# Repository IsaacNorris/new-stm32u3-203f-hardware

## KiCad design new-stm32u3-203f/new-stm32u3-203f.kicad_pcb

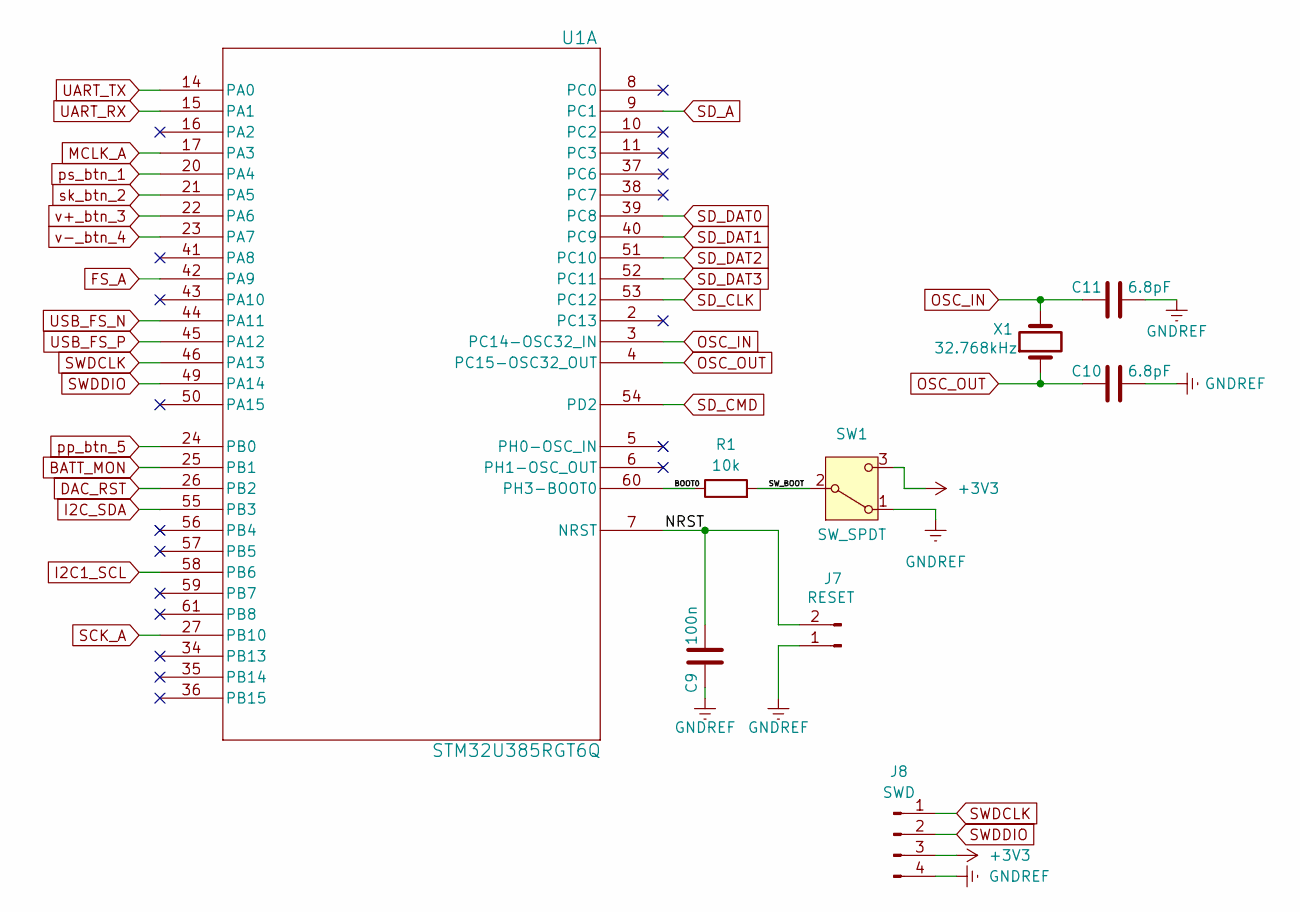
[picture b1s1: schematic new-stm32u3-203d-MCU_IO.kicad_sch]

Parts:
C9: 100n; C_0603_1608Metric
C10, C11: 6.8pF; C_0603_1608Metric
J7: RESET; PinHeader_1x02_P1.00mm_Vertical
J8: SWD; PinHeader_1x04_P2.54mm_Vertical
R1: 10k; R_0603_1608Metric
SW1: SW_SPDT; SW_CJS-1200TA
U1: STM32U385RGT6Q; LQFP-64_10x10mm_P0.5mm
X1: 32.768kHz; Crystal_SMD_3215-2Pin_3.2x1.5mm

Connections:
/MCU_IO/BOOT0: R1.1, U1.60 (PH3-BOOT0)
/MCU_IO/NRST: C9.2, J7.2, U1.7 (NRST)
/MCU_IO/SW_BOOT: R1.2, SW1.2 (B)
AVDD: J8.3, SW1.3 (C); also elsewhere on the board
BATT_MON: U1.25 (PB1); also elsewhere on the board
DAC_RST: U1.26 (PB2); also elsewhere on the board
FS_A: U1.42 (PA9); also elsewhere on the board
I2C1_SCL: U1.58 (PB6); also elsewhere on the board
I2C_SDA: U1.55 (PB3); also elsewhere on the board
MCLK_A: U1.17 (PA3); also elsewhere on the board
OSC_IN: C11.1, U1.3 (PC14-OSC32_IN), X1.2
OSC_OUT: C10.1, U1.4 (PC15-OSC32_OUT), X1.1
SCK_A: U1.27 (PB10); also elsewhere on the board
SD_A: U1.9 (PC1); also elsewhere on the board
SD_CLK: U1.53 (PC12); also elsewhere on the board
SD_CMD: U1.54 (PD2); also elsewhere on the board
SD_DAT0: U1.39 (PC8); also elsewhere on the board
SD_DAT1: U1.40 (PC9); also elsewhere on the board
SD_DAT2: U1.51 (PC10); also elsewhere on the board
SD_DAT3: U1.52 (PC11); also elsewhere on the board
SWDCLK: J8.1, U1.46 (PA13)
SWDDIO: J8.2, U1.49 (PA14)
UART_RX: U1.15 (PA1); also elsewhere on the board
UART_TX: U1.14 (PA0); also elsewhere on the board
UBS_D+: U1.45 (PA12); also elsewhere on the board
USB_D-: U1.44 (PA11); also elsewhere on the board
USB_GND: C9.1, C10.2, C11.2, J7.1, J8.4, SW1.1 (A); also elsewhere on the board
pp_btn_5: U1.24 (PB0); also elsewhere on the board
ps_btn_1: U1.20 (PA4); also elsewhere on the board
sk_btn_2: U1.21 (PA5); also elsewhere on the board
v+_btn_3: U1.22 (PA6); also elsewhere on the board
v-_btn_4: U1.23 (PA7); also elsewhere on the board

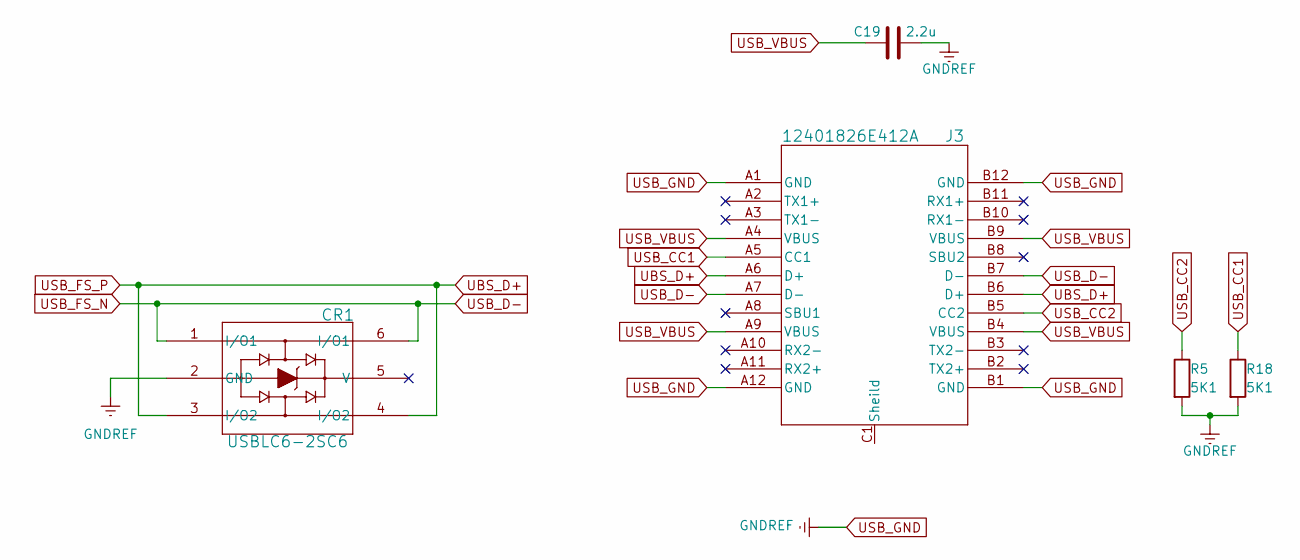
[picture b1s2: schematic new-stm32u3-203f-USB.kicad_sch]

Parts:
C19: 2.2u; C_0603_1608Metric
CR1: USBLC6-2SC6; SOT23-6L_STM
J3: 12401826E412A; 12401826_AMP
R5, R18: 5K1; R_0603_1608Metric

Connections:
UBS_D+: CR1.3 (I/O2), CR1.4 (I/O2), J3.A6 (D+), J3.B6 (D+); also elsewhere on the board
USB_3v3_EN: C19.1, J3.A4 (VBUS), J3.A9 (VBUS), J3.B4 (VBUS), J3.B9 (VBUS); also elsewhere on the board
USB_CC1: J3.A5 (CC1), R18.1
USB_CC2: J3.B5 (CC2), R5.1
USB_D-: CR1.1 (I/O1), CR1.6 (I/O1), J3.A7 (D-), J3.B7 (D-); also elsewhere on the board
USB_GND: C19.2, CR1.2 (GND), J3.A1 (GND), J3.A12 (GND), J3.B1 (GND), J3.B12 (GND), R5.2, R18.2; also elsewhere on the board

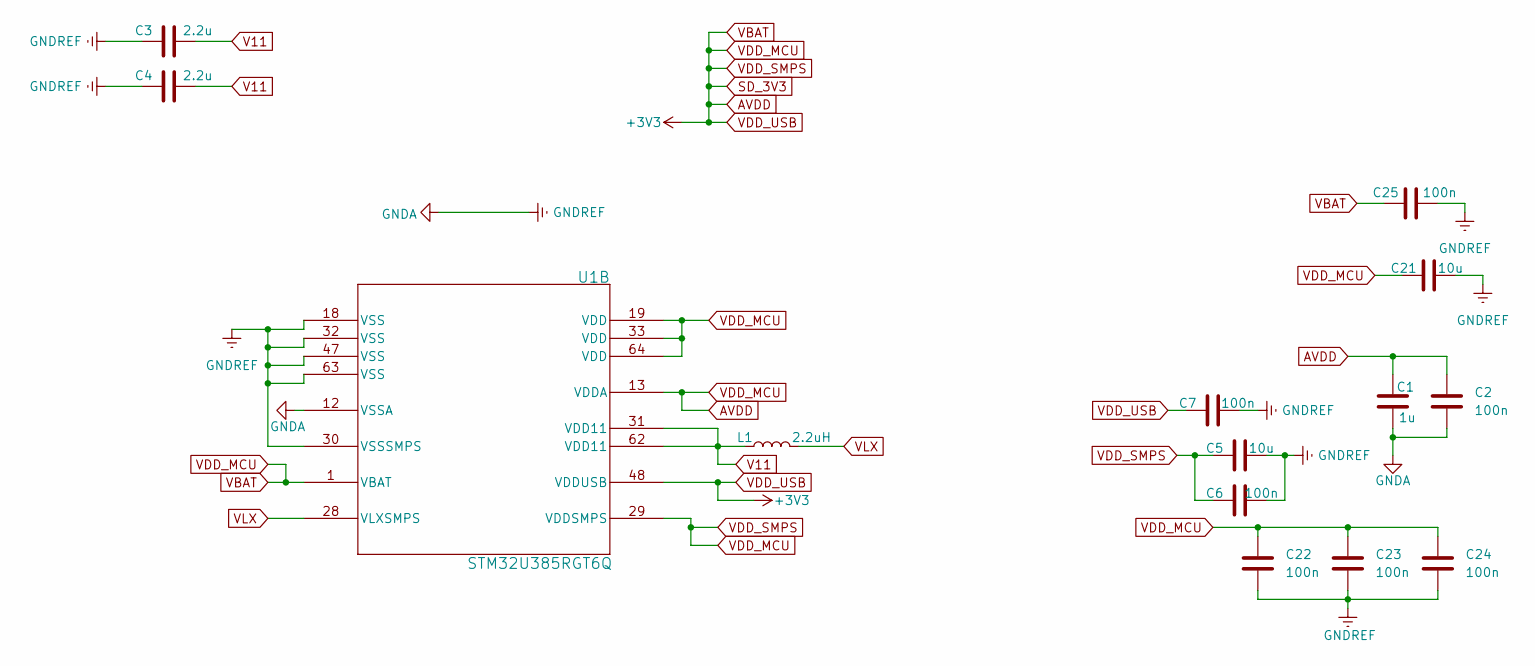
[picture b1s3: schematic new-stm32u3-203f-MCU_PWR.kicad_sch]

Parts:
C1: 1u; C_0603_1608Metric
C2, C6, C7, C22, C23, C24, C25: 100n; C_0603_1608Metric
C3, C4: 2.2u; C_0603_1608Metric
C5, C21: 10u; C_0603_1608Metric
L1: 2.2uH; L_0603_1608Metric
U1: STM32U385RGT6Q; LQFP-64_10x10mm_P0.5mm

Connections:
AVDD: C1.2, C2.2, C5.2, C6.2, C7.2, C21.2, C22.2, C23.2, C24.2, C25.2, U1.1 (VBAT), U1.13 (VDDA), U1.19 (VDD), U1.29 (VDDSMPS), U1.33 (VDD), U1.48 (VDDUSB), U1.64 (VDD); also elsewhere on the board
USB_GND: C1.1, C2.1, C3.2, C4.2, C5.1, C6.1, C7.1, C21.1, C22.1, C23.1, C24.1, C25.1, U1.12 (VSSA), U1.18 (VSS), U1.30 (VSSSMPS), U1.32 (VSS), U1.47 (VSS), U1.63 (VSS); also elsewhere on the board
V11: C3.1, C4.1, L1.1, U1.31 (VDD11), U1.62 (VDD11)
VLX: L1.2, U1.28 (VLXSMPS)

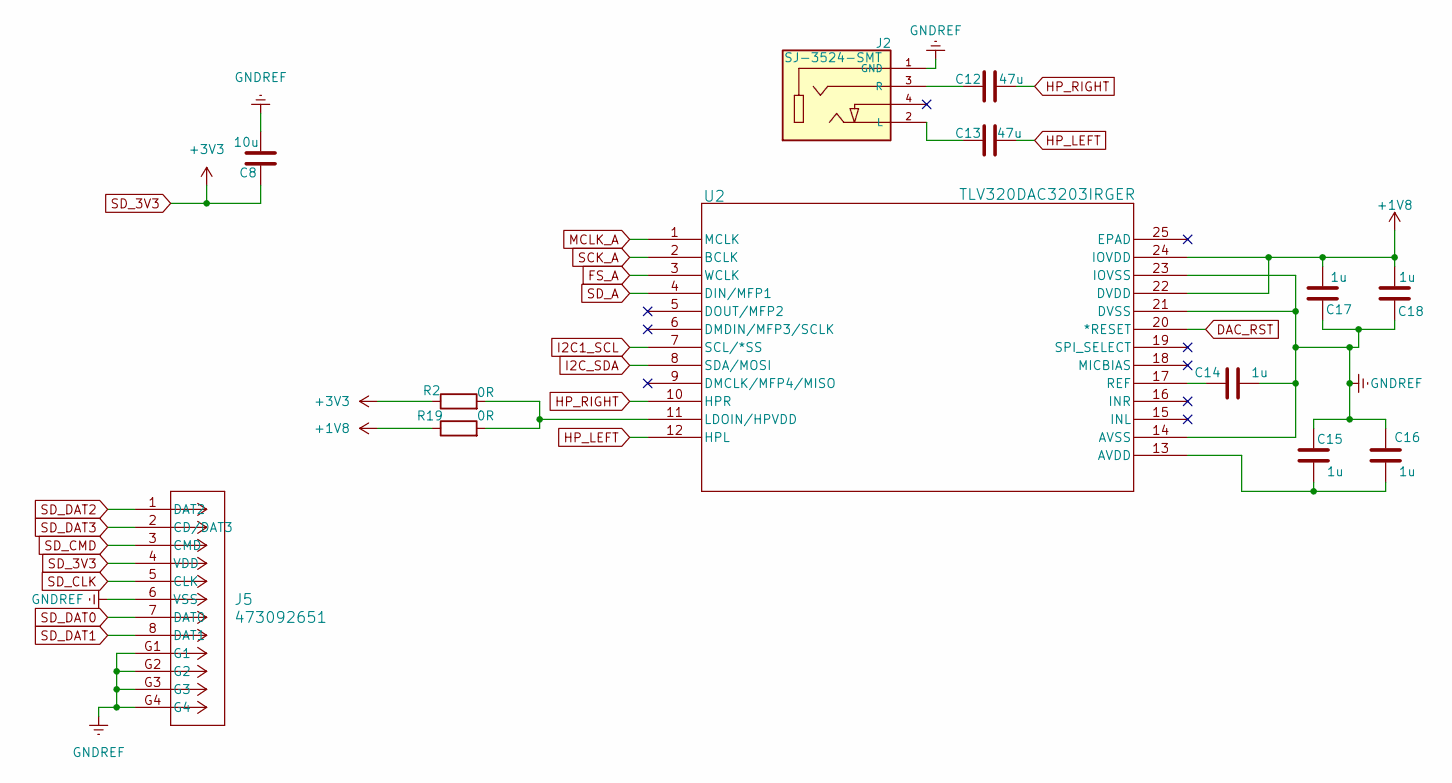
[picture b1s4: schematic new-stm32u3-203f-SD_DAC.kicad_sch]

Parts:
C8: 10u; C_0603_1608Metric
C12, C13: 47u; C_0603_1608Metric
C14, C15, C16, C17, C18: 1u; C_0603_1608Metric
J2: SJ-3524-SMT; Jack_3.5mm_CUI_SJ-3524-SMT_Horizontal; PARTREV 1.03
J5: 473092651; CONN12_47309-2651_MOL
R2, R19: 0R; R_0603_1608Metric
U2: TLV320DAC3203IRGER; Texas_RGE0024C_VQFN-24-1EP_4x4mm_P0.5mm_EP2.1x2.1mm

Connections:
+1V8: C17.2, C18.2, R19.1, U2.22 (DVDD), U2.24 (IOVDD); also elsewhere on the board
AVDD: C8.2, J5.4 (VDD), R2.1; also elsewhere on the board
DAC_RST: U2.20 (*RESET); also elsewhere on the board
FS_A: U2.3 (WCLK); also elsewhere on the board
HP_LEFT: C13.2, U2.12 (HPL)
HP_RIGHT: C12.2, U2.10 (HPR)
I2C1_SCL: U2.7 (SCL/*SS); also elsewhere on the board
I2C_SDA: U2.8 (SDA/MOSI); also elsewhere on the board
MCLK_A: U2.1 (MCLK); also elsewhere on the board
unnamed: C13.1, J2.2 (L), J2.T
unnamed: C12.1, J2.3 (R), J2.R
unnamed: C15.2, C16.2, U2.13 (AVDD)
unnamed: R2.2, R19.2, U2.11 (LDOIN/HPVDD)
unnamed: C14.1, U2.17 (REF)
SCK_A: U2.2 (BCLK); also elsewhere on the board
SD_A: U2.4 (DIN/MFP1); also elsewhere on the board
SD_CLK: J5.5 (CLK); also elsewhere on the board
SD_CMD: J5.3 (CMD); also elsewhere on the board
SD_DAT0: J5.7 (DAT0); also elsewhere on the board
SD_DAT1: J5.8 (DAT1); also elsewhere on the board
SD_DAT2: J5.1 (DAT2); also elsewhere on the board
SD_DAT3: J5.2 (CD/DAT3); also elsewhere on the board
USB_GND: C8.1, C14.2, C15.1, C16.1, C17.1, C18.1, J2.1 (GND), J2.S, J5.6 (VSS), J5.G1, J5.G2, J5.G3, J5.G4, U2.14 (AVSS), U2.21 (DVSS), U2.23 (IOVSS); also elsewhere on the board

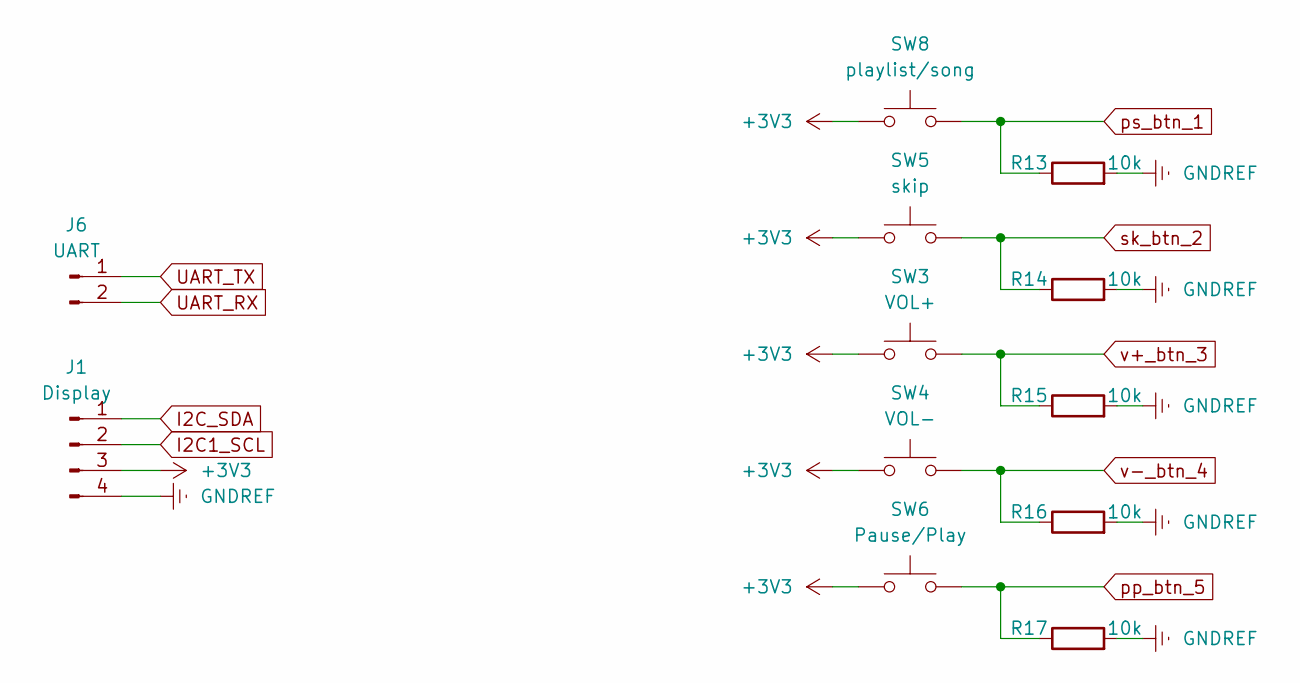
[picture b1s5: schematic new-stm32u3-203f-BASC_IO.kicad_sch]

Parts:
J1: Display; PinHeader_1x04_P2.54mm_Vertical
J6: UART; PinHeader_1x02_P2.54mm_Vertical
R13, R14, R15, R16, R17: 10k; R_0603_1608Metric
SW3: VOL+; Panasonic_EVQPUL_EVQPUC
SW4: VOL-; Panasonic_EVQPUL_EVQPUC
SW5: skip; Panasonic_EVQPUL_EVQPUC
SW6: Pause/Play; Panasonic_EVQPUL_EVQPUC
SW8: playlist/song; Panasonic_EVQPUL_EVQPUC

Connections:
AVDD: J1.3, SW3.1, SW4.1, SW5.1, SW6.1, SW8.1; also elsewhere on the board
I2C1_SCL: J1.2; also elsewhere on the board
I2C_SDA: J1.1; also elsewhere on the board
UART_RX: J6.2; also elsewhere on the board
UART_TX: J6.1; also elsewhere on the board
USB_GND: J1.4, R13.2, R14.2, R15.2, R16.2, R17.2; also elsewhere on the board
pp_btn_5: R17.1, SW6.2; also elsewhere on the board
ps_btn_1: R13.1, SW8.2; also elsewhere on the board
sk_btn_2: R14.1, SW5.2; also elsewhere on the board
v+_btn_3: R15.1, SW3.2; also elsewhere on the board
v-_btn_4: R16.1, SW4.2; also elsewhere on the board

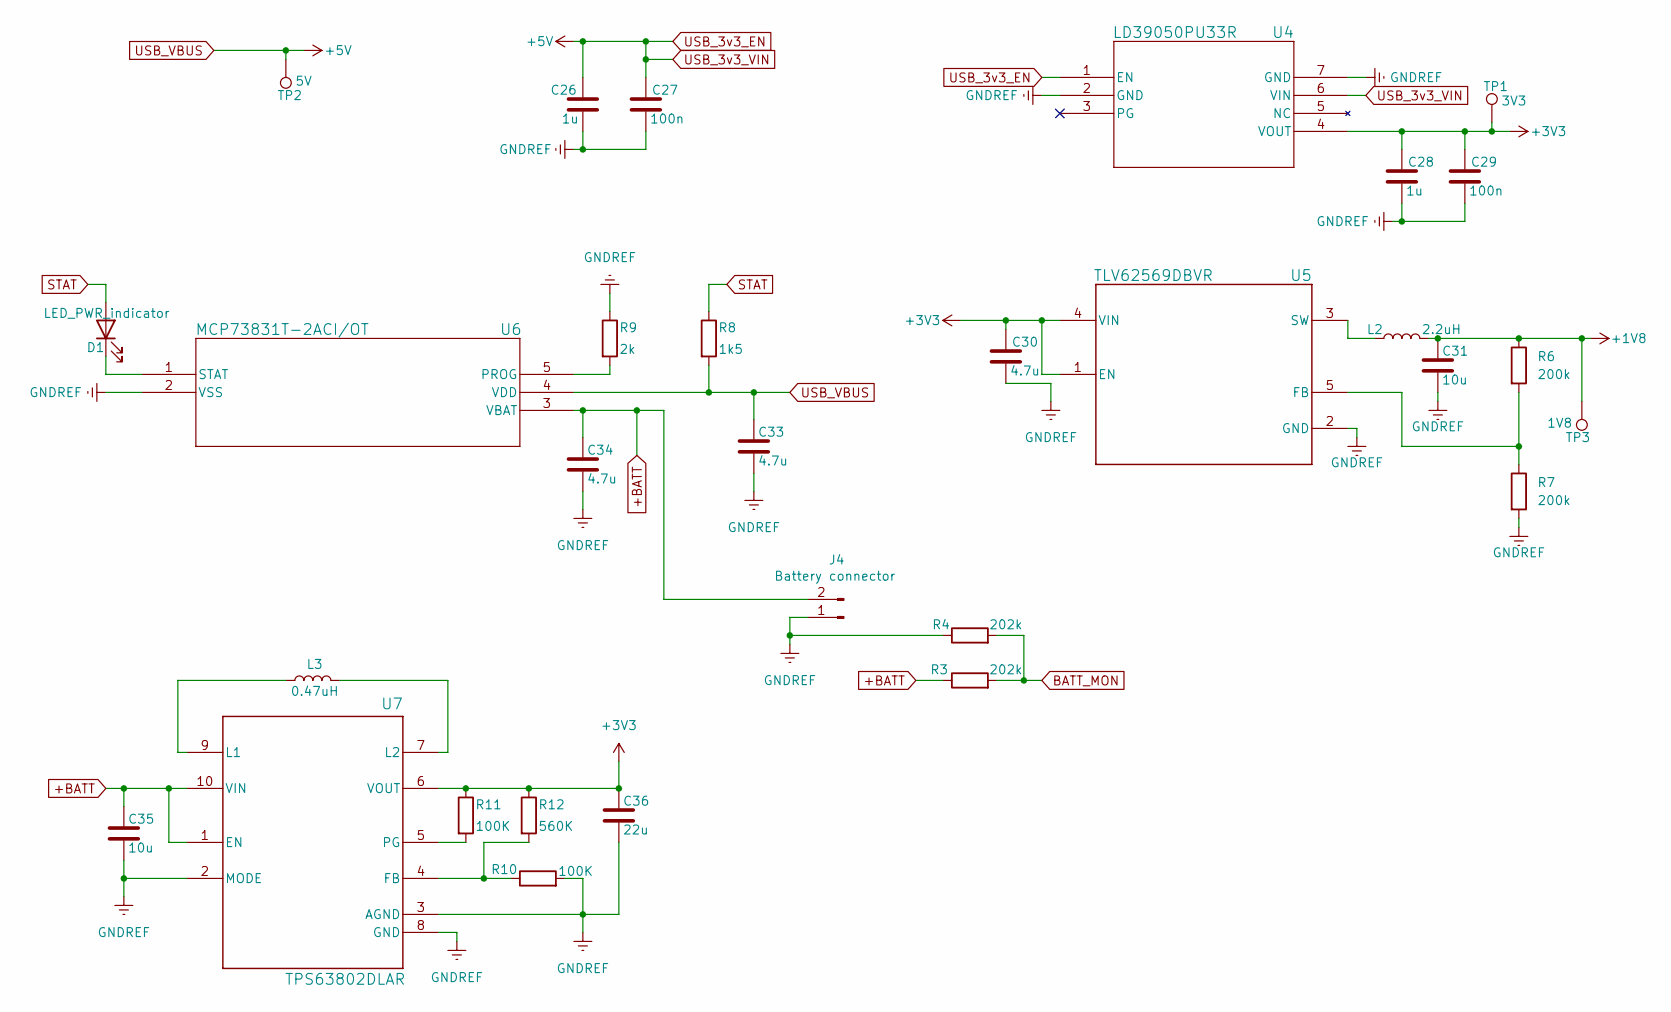
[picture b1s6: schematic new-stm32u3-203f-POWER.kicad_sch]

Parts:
C26, C28: 1u; C_0603_1608Metric
C27, C29: 100n; C_0603_1608Metric
C30, C33, C34: 4.7u; C_0603_1608Metric
C31, C35: 10u; C_0603_1608Metric
C36: 22u; C_0603_1608Metric
D1: LED_PWR_indicator; LED_0603_1608Metric
J4: Battery connector; PinHeader_1x02_P2.54mm_Vertical
L2: 2.2uH; L_0603_1608Metric
L3: 0.47uH; L_0603_1608Metric
R3, R4: 202k; R_0603_1608Metric
R6, R7: 200k; R_0603_1608Metric
R8: 1k5; R_0603_1608Metric
R9: 2k; R_0603_1608Metric
R10, R11: 100K; R_0603_1608Metric
R12: 560K; R_0603_1608Metric
TP1: 3V3; TestPoint_Pad_D1.0mm
TP2: 5V; TestPoint_Pad_D1.0mm
TP3: 1V8; TestPoint_Pad_D1.0mm
U4: LD39050PU33R; DFN-6-1EP_3x3mm_P0.95mm_EP1.7x2.6mm
U5: TLV62569DBVR; SOT-23-5
U6: MCP73831T-2ACI/OT; SOT-23-5
U7: TPS63802DLAR; DLA0010A

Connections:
+1V8: C31.2, L2.2, R6.1, TP3.1; also elsewhere on the board
+BATT: C34.2, C35.2, J4.2, R3.1, U6.3 (VBAT), U7.1 (EN), U7.10 (VIN)
AVDD: C28.2, C29.2, C30.2, C36.2, R11.1, R12.1, TP1.1, U4.4 (VOUT), U5.1 (EN), U5.4 (VIN), U7.6 (VOUT); also elsewhere on the board
BATT_MON: R3.2, R4.2; also elsewhere on the board
unnamed: D1.1 (K), U6.1 (STAT)
unnamed: R6.2, R7.1, U5.5 (FB)
unnamed: L2.1, U5.3 (SW)
unnamed: R9.2, U6.5 (PROG)
unnamed: R10.1, R12.2, U7.4 (FB)
unnamed: L3.1, U7.9 (L1)
unnamed: L3.2, U7.7 (L2)
unnamed: R11.2, U7.5 (PG)
STAT: D1.2 (A), R8.1
USB_3v3_EN: C26.2, C27.2, C33.2, R8.2, TP2.1, U4.1 (EN), U4.6 (VIN), U6.4 (VDD); also elsewhere on the board
USB_GND: C26.1, C27.1, C28.1, C29.1, C30.1, C31.1, C33.1, C34.1, C35.1, C36.1, J4.1, R4.1, R7.2, R9.1, R10.2, U4.2 (GND), U4.7 (GND), U5.2 (GND), U6.2 (VSS), U7.2 (MODE), U7.3 (AGND), U7.8 (GND); also elsewhere on the board

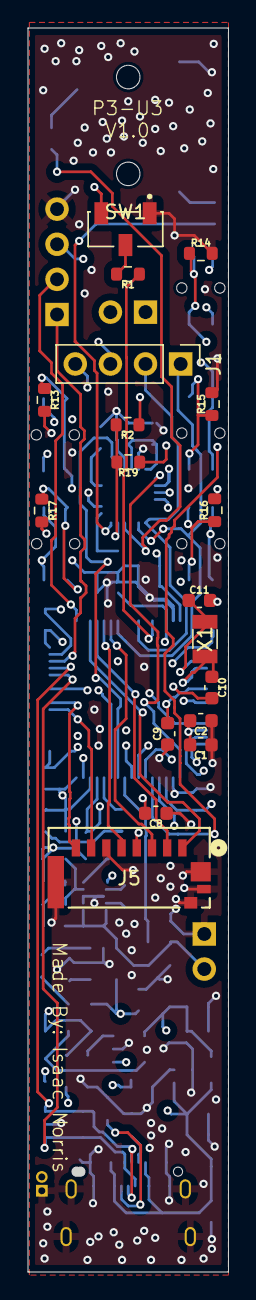
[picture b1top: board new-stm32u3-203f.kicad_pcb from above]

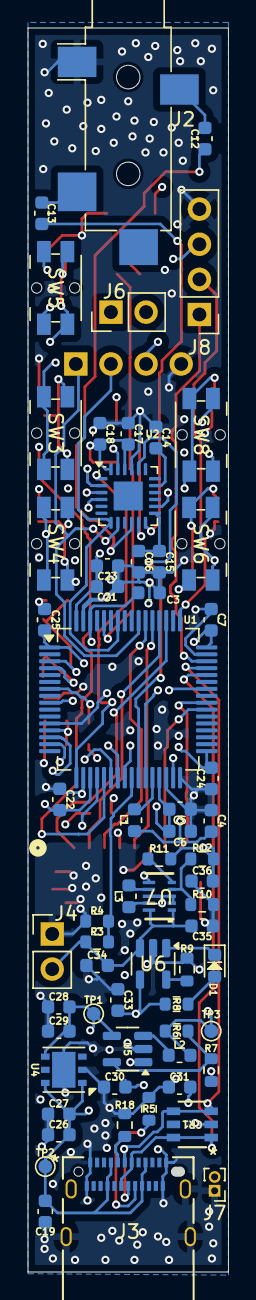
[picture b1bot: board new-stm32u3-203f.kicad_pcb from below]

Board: 6 copper layers, 13.9 x 89.4 mm, 82 parts (64 on the bottom side), 55 nets.

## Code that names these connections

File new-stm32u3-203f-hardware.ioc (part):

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Mcu.Name=STM32U385RGTxQ
Mcu.Package=LQFP64
Mcu.UserName=STM32U385RGTxQ
PA0.Mode=Asynchronous
PA0.Signal=UART4_TX
PA1.Mode=Asynchronous
PA1.Signal=UART4_RX
PA11.Mode=Device
PA11.Signal=USB_DM
PA12.Mode=Device
PA12.Signal=USB_DP
PA13\ (JTMS/SWDIO).Mode=Serial_Wire
PA13\ (JTMS/SWDIO).Signal=DEBUG_JTMS-SWDIO
PA14\ (JTCK/SWCLK).Mode=Serial_Wire
PA14\ (JTCK/SWCLK).Signal=DEBUG_JTCK-SWCLK
PA3.Mode=SAI_A_MasterWithClock
PA3.Signal=SAI1_MCLK_A
PA4.Signal=GPIO_Input
PA5.Signal=GPIO_Input
PA6.Signal=GPIO_Input
PA7.Signal=GPIO_Input
PA9.Mode=SAI_A_MasterWithClock
PA9.Signal=SAI1_FS_A
PB0.Signal=GPIO_Input
PB1.Mode=IN14-Single-Ended
PB1.Signal=ADC1_IN14
PB10.Mode=SAI_A_MasterWithClock
PB10.Signal=SAI1_SCK_A
PB2.Signal=GPIO_Output
PB6.Mode=I2C
PB6.Signal=I2C1_SCL
PB7.Mode=I2C
PB7.Signal=I2C1_SDA
PC10.Mode=SD_4_bits_Wide_bus
PC10.Signal=SDMMC1_D2
PC11.Mode=SD_4_bits_Wide_bus
PC11.Signal=SDMMC1_D3
PC12.Mode=SD_4_bits_Wide_bus
PC12.Signal=SDMMC1_CK
PC14-OSC32_IN\ (PC14).Mode=LSE-External-Oscillator
PC14-OSC32_IN\ (PC14).Signal=RCC_OSC32_IN
PC15-OSC32_OUT\ (PC15).Mode=LSE-External-Oscillator
PC15-OSC32_OUT\ (PC15).Signal=RCC_OSC32_OUT
PC3.Mode=SAI_A_MasterWithClock
PC3.Signal=SAI1_SD_A
PC8.Mode=SD_4_bits_Wide_bus
PC8.Signal=SDMMC1_D0
PC9.Mode=SD_4_bits_Wide_bus
PC9.Signal=SDMMC1_D1
PD2.Mode=SD_4_bits_Wide_bus
PD2.Signal=SDMMC1_CMD
RCC.HSE_VALUE=16000000
RCC.SYSCLKFreq_VALUE=96000000
board=custom

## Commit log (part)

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2026-01-22 initialised the repo
2026-01-23 removed bad temp file
2026-01-23 added some usb stuff, changed to 64 pinout.
2026-01-23 updated properly
2026-01-23 added 64pinout ioc
2026-01-24 mcu power finished
2026-01-24 finished the sd card wiring up.
2026-01-24 made some prograss on the usb/power stuff.
2026-01-25 made some progress on the board.
2026-01-25 removed temp files
2026-01-26 finished the USB page of the eval board. now need to do power for 3v3, 5v, & 1v8
2026-01-26 added 1v8 power
2026-01-26 moved some studd around.
2026-01-27 did the power pins
2026-01-27 moved sections to their own sheets. much cleaner now :)
2026-01-27 added battery charging circuit
2026-01-27 added resources folder
2026-01-28 moved over to new sd card stuff
2026-01-28 added buttons, added uart, added display.
2026-01-29 finished the schematic, just need someone to review it :)
2026-01-30 added reset button. asigned footprints.
2026-01-30 made some progress on the pcb
2026-01-31 made some progress on the pcb layout
2026-02-01 made some progress witht he layout.
2026-02-02 moved over to just using direct usb 2.0, made progress on pcb layout
2026-02-02 finished the layout of the pcb
2026-02-03 made some progress on layout and routes.
2026-02-04 added in 0r to choose ldoin of dac
2026-02-04 made routing progress
2026-02-04 made some better progress routing
2026-02-05 restarted routing and started using 6 layers and power planes.
2026-02-05 finished routing, need angus to check
2026-02-06 ficxed all the vias and some routing, will need to add in ground stitching
2026-02-10 added usb sheilding and more stiching vias
2026-02-12 fixed silkscreen.
2026-02-16 made up to date.
2026-02-20 fixed some of the drc erros will need to complete more.
2026-02-20 added digikey recipt.
2026-02-20 finished more errors, started adding extra stuff.
2026-02-20 fixed drc and some other things.
2026-02-23 did some hardware fixes.
2026-05-06 added in TODO.txt
